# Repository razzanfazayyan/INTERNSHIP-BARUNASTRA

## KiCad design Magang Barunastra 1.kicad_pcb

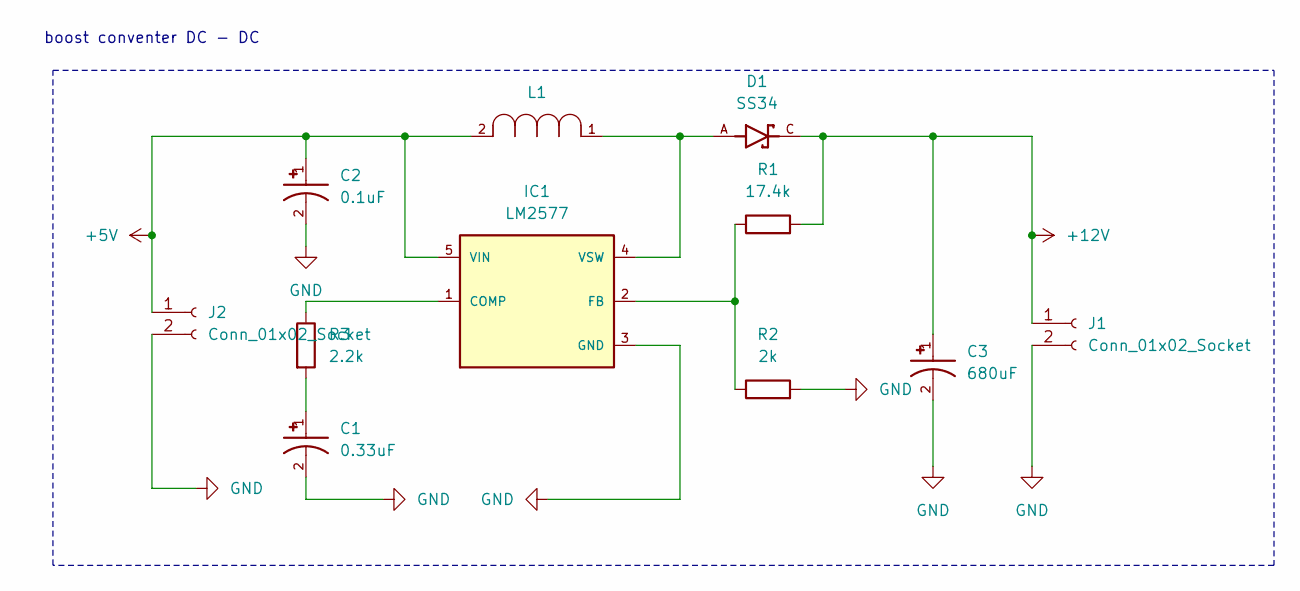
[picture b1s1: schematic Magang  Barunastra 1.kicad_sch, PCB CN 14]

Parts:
C1: 0.33uF; CAP_EEEFK1C101V; PARTREV 10-Oct-19
C2: 0.1uF; CAP_EEEFK1C101V; PARTREV 10-Oct-19
C3: 680uF; CAP_EEEFK1C101V; PARTREV 10-Oct-19
D1: SS34; DIO_SS34; PARTREV S2311
IC1: LM2577; TO263-5
J1, J2: Conn_01x02_Socket; PhoenixContact_GMSTBVA_2,5_2-G-7,62_1x02_P7.62mm_Vertical
L1: 100uH; IND_BOURNS_SRR1260; MANUFACTURER_PART_NUMBER SRR1260-101M; DIGI-KEY_PART_NUMBER_1 SRR1260-101MCT-ND
R1: 17.4k; R_1206_3216Metric_Pad1.30x1.75mm_HandSolder
R2: 2k; R_1206_3216Metric_Pad1.30x1.75mm_HandSolder
R3: 2.2k; R_1206_3216Metric_Pad1.30x1.75mm_HandSolder

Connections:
+5V: C2.1, IC1.5 (VIN), J2.1, L1.2
+12V: C3.1, D1.C, J1.1, R1.2
GND: C1.2, C2.2, C3.2, IC1.3 (GND), J1.2, J2.2, R2.2
unnamed: C1.1, R3.2
unnamed: IC1.1 (COMP), R3.1
unnamed: IC1.2 (FB), R1.1, R2.1
unnamed: D1.A, IC1.4 (VSW), L1.1

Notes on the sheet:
boost conventer DC - DC

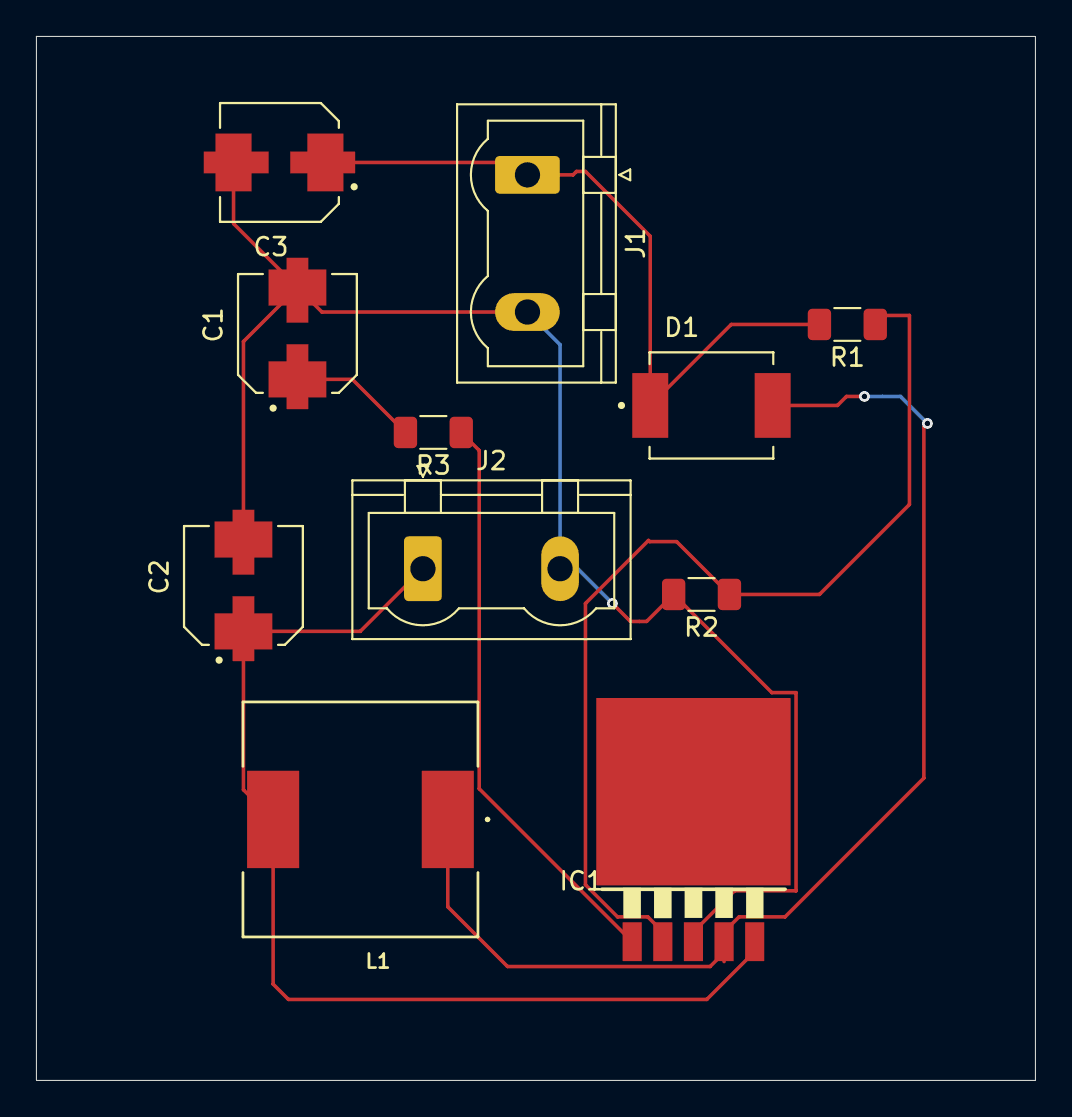
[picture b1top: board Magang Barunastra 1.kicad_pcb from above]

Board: 2 copper layers, 55.5 x 58.0 mm, 11 parts (0 on the bottom side), 7 nets.

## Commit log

2024-11-23 zoom hari rabu

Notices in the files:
parts and their libraries:
COPYRIGHT: Copyright (C) 2022 Ultra Librarian. All rights reserved.
